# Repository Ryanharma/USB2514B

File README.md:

# USB2514B
USB Hub design project on Kicad => schematic + pcb layout (beginner)

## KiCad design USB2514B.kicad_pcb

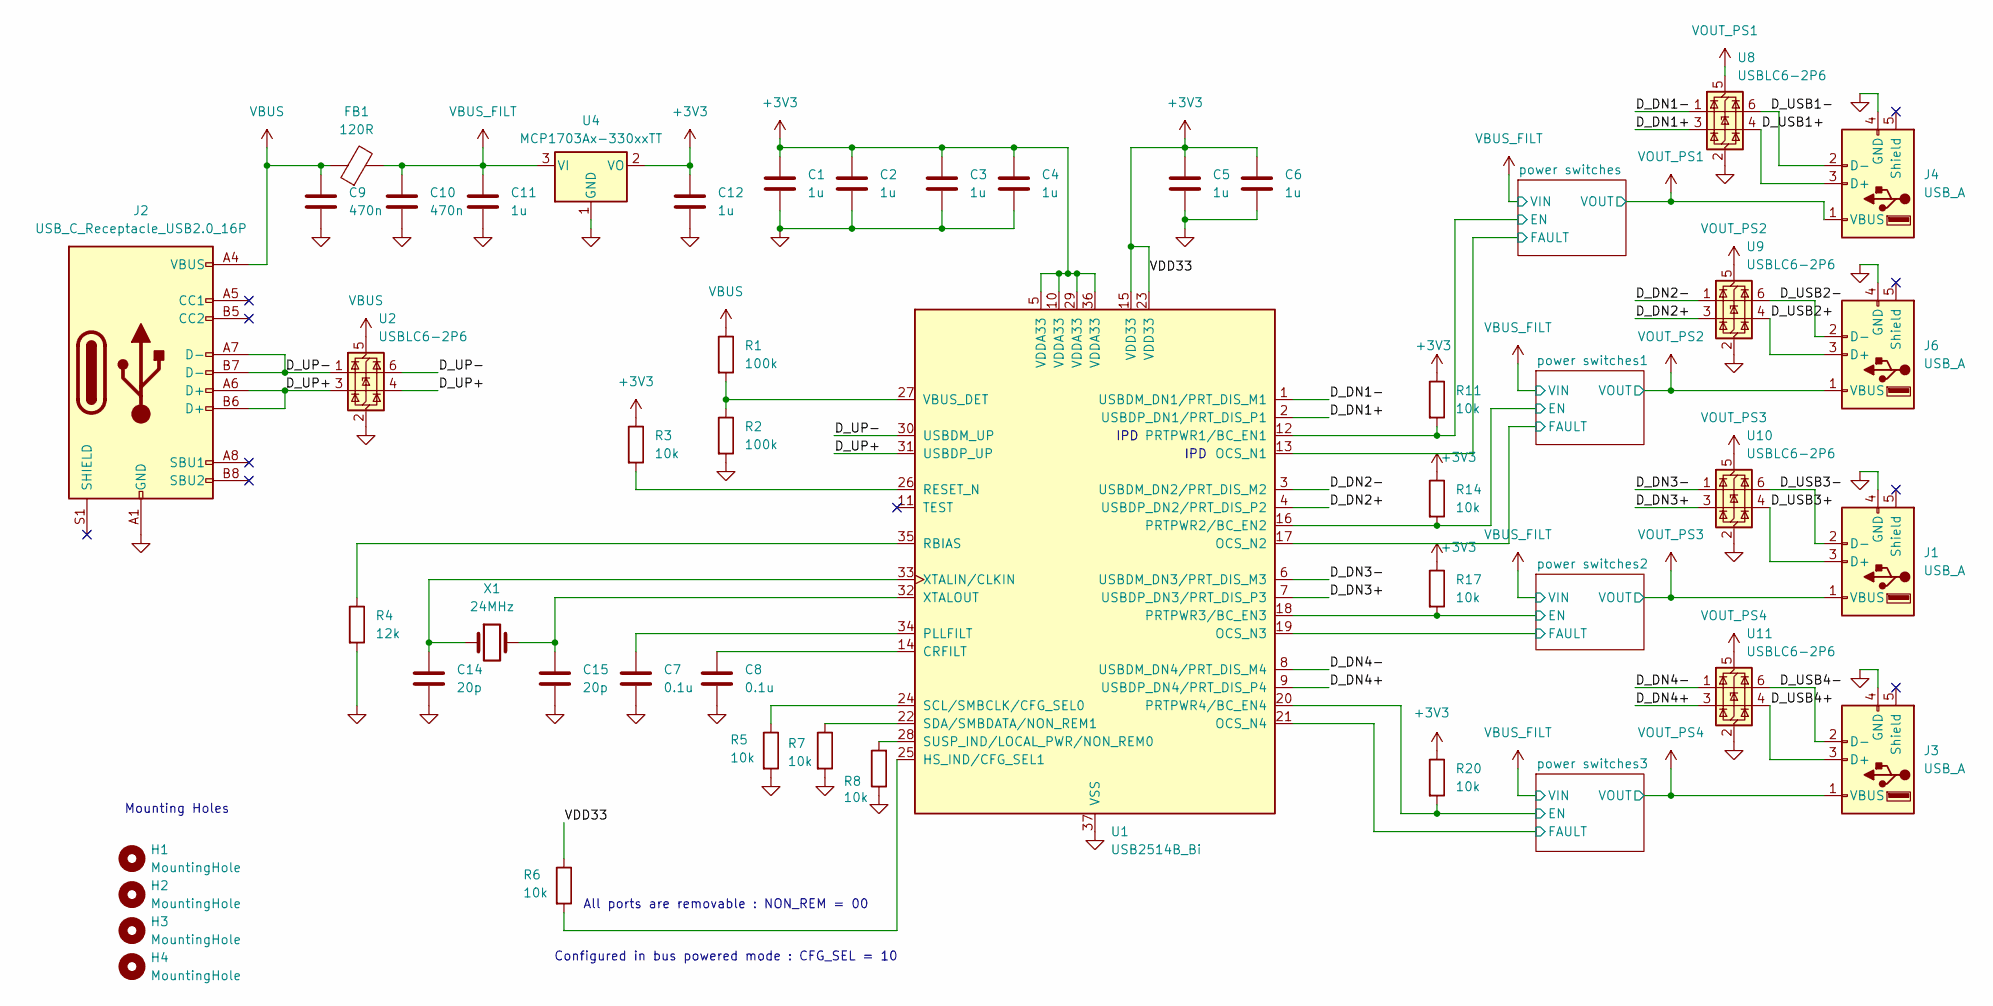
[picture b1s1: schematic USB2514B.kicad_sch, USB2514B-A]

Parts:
C1, C2, C3, C4, C5, C6, C11, C12: 1u; C_0402_1005Metric_Pad0.74x0.62mm_HandSolder; Manufacturer Part Number GXT155R61C105KE01D; LCSC Part # C363938
C7, C8: 0.1u; C_1206_3216Metric_Pad1.33x1.80mm_HandSolder; Manufacturer Part Number 12065C104J4Z2A; LCSC Part # C6648471
C9, C10: 470n; C_0402_1005Metric_Pad0.74x0.62mm_HandSolder; Manufacturer Part Number GXT155R61C474KE01D; LCSC Part # C126625
C14, C15: 20p; C_0402_1005Metric_Pad0.74x0.62mm_HandSolder; Manufacturer Part Number GCM1555C1H200FA16D; LCSC Part # C1554
FB1: 120R; C_0603_1608Metric_Pad1.08x0.95mm_HandSolder; Manufacturer Part Number BLM18PG121SN1D; LCSC Part # C14709
H1, H2, H3, H4: MountingHole; MountingHole_2.2mm_M2
J1, J3, J4, J6: USB_A; USB_A_Molex_67643_Horizontal; Manufacturer Part Number 10502029K901A; LCSC Part # C2345
J2: USB_C_Receptacle_USB2.0_16P; USB_C_Receptacle_GCT_USB4105-xx-A_16P_TopMnt_Horizontal; Manufacturer Part Number UJ20-C-H-C-4-SMT-TR; LCSC Part # C36601498
R1: 100k; R_0402_1005Metric_Pad0.72x0.64mm_HandSolder; Manufacturer Part Number ERJ-H2RF1003X; LCSC Part # C25741
R2: 100k; R_0402_1005Metric_Pad0.72x0.64mm_HandSolder; Manufacturer Part Number RT0402WRD0710KL; LCSC Part # C25741
R3, R5, R6, R7, R8, R11, R14, R17, R20: 10k; R_0402_1005Metric_Pad0.72x0.64mm_HandSolder; Manufacturer Part Number RT0402WRD0710KL; LCSC Part # C25531
R4: 12k; R_0402_1005Metric_Pad0.72x0.64mm_HandSolder; Manufacturer Part Number AR0402FR-0712KL; LCSC Part # C144798
U1: USB2514B_Bi; QFN-36-1EP_6x6mm_P0.5mm_EP3.7x3.7mm; Manufacturer Part Number USB2514BI-AEZG-TR; LCSC Part # C58940
U2, U8, U9, U10, U11: USBLC6-2P6; SOT-666; Manufacturer Part Number USBLC6-2P6; LCSC Part # C15999
U4: MCP1703Ax-330xxTT; SOT-23; Manufacturer Part Number MCP1703AT-3302E/CBVAO; LCSC Part # C5236965
X1: 24MHz; Crystal_SMD_7050-2Pin_7.0x5.0mm_HandSoldering; Manufacturer Part Number ABLS7M2-24.000MHZ-D-2Y-T; LCSC Part # C6487089

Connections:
+3V3: C1.1, C2.1, C3.1, C4.1, C5.1, C6.1, C12.1, R3.1, R6.1, R11.1, R14.1, R17.1, R20.1, U1.5 (VDDA33), U1.10 (VDDA33), U1.15 (VDD33), U1.23 (VDD33), U1.29 (VDDA33), U1.36 (VDDA33), U4.2 (VO)
/D_DN1+: U1.2 (USBDP_DN1/PRT_DIS_P1), U8.3 (I/O2)
/D_DN1-: U1.1 (USBDM_DN1/PRT_DIS_M1), U8.1 (I/O1)
/D_DN2+: U1.4 (USBDP_DN2/PRT_DIS_P2), U9.3 (I/O2)
/D_DN2-: U1.3 (USBDM_DN2/PRT_DIS_M2), U9.1 (I/O1)
/D_DN3+: U1.7 (USBDP_DN3/PRT_DIS_P3), U10.3 (I/O2)
/D_DN3-: U1.6 (USBDM_DN3/PRT_DIS_M3), U10.1 (I/O1)
/D_DN4+: U1.9 (USBDP_DN4/PRT_DIS_P4), U11.3 (I/O2)
/D_DN4-: U1.8 (USBDM_DN4/PRT_DIS_M4), U11.1 (I/O1)
/D_UP+: J2.A6 (D+), J2.B6 (D+), U1.31 (USBDP_UP), U2.3 (I/O2), U2.4 (I/O2)
/D_UP-: J2.A7 (D-), J2.B7 (D-), U1.30 (USBDM_UP), U2.1 (I/O1), U2.6 (I/O1)
/D_USB1+: J4.3 (D+), U8.4 (I/O2)
/D_USB1-: J4.2 (D-), U8.6 (I/O1)
/D_USB2+: J6.3 (D+), U9.4 (I/O2)
/D_USB2-: J6.2 (D-), U9.6 (I/O1)
/D_USB3+: J1.3 (D+), U10.4 (I/O2)
/D_USB3-: J1.2 (D-), U10.6 (I/O1)
/D_USB4+: J3.3 (D+), U11.4 (I/O2)
/D_USB4-: J3.2 (D-), U11.6 (I/O1)
/power switches1/EN: R14.2, U1.16 (PRTPWR2/BC_EN2); also elsewhere on the board
/power switches1/FAULT: U1.17 (OCS_N2); also elsewhere on the board
/power switches2/EN: R17.2, U1.18 (PRTPWR3/BC_EN3); also elsewhere on the board
/power switches2/FAULT: U1.19 (OCS_N3); also elsewhere on the board
/power switches3/EN: R20.2, U1.20 (PRTPWR4/BC_EN4); also elsewhere on the board
/power switches3/FAULT: U1.21 (OCS_N4); also elsewhere on the board
/power switches/EN: R11.2, U1.12 (PRTPWR1/BC_EN1); also elsewhere on the board
/power switches/FAULT: U1.13 (OCS_N1); also elsewhere on the board
GND: C1.2, C2.2, C3.2, C4.2, C5.2, C6.2, C7.2, C8.2, C9.2, C10.2, C11.2, C12.2, C14.2, C15.2, J1.4 (GND), J2.A1 (GND), J2.A12 (GND), J2.B1 (GND), J2.B12 (GND), J3.4 (GND), J4.4 (GND), J6.4 (GND), R2.2, R4.2, R5.2, R7.2, R8.1, U1.37 (VSS), U2.2 (GND), U4.1 (GND), U8.2 (GND), U9.2 (GND), U10.2 (GND), U11.2 (GND); also elsewhere on the board
unnamed: C8.1, U1.14 (CRFILT)
unnamed: R6.2, U1.25 (HS_IND/CFG_SEL1)
unnamed: C7.1, U1.34 (PLLFILT)
unnamed: R4.1, U1.35 (RBIAS)
unnamed: R3.2, U1.26 (RESET_N)
unnamed: R5.1, U1.24 (SCL/SMBCLK/CFG_SEL0)
unnamed: R7.1, U1.22 (SDA/SMBDATA/NON_REM1)
unnamed: R8.2, U1.28 (SUSP_IND/LOCAL_PWR/NON_REM0)
unnamed: R1.2, R2.1, U1.27 (VBUS_DET)
unnamed: C14.1, U1.33 (XTALIN/CLKIN), X1.1
unnamed: C15.1, U1.32 (XTALOUT), X1.2
VBUS: C9.1, FB1.1, J2.A4 (VBUS), J2.A9 (VBUS), J2.B4 (VBUS), J2.B9 (VBUS), R1.1, U2.5 (VBUS)
VBUS_FILT: C10.1, C11.1, FB1.2, U4.3 (VI); also elsewhere on the board
VOUT_PS1: J4.1 (VBUS), U8.5 (VBUS); also elsewhere on the board
VOUT_PS2: J6.1 (VBUS), U9.5 (VBUS); also elsewhere on the board
VOUT_PS3: J1.1 (VBUS), U10.5 (VBUS); also elsewhere on the board
VOUT_PS4: J3.1 (VBUS), U11.5 (VBUS); also elsewhere on the board

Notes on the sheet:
All ports are removable : NON_REM = 00
Mounting Holes
IPD
Configured in bus powered mode : CFG_SEL = 10

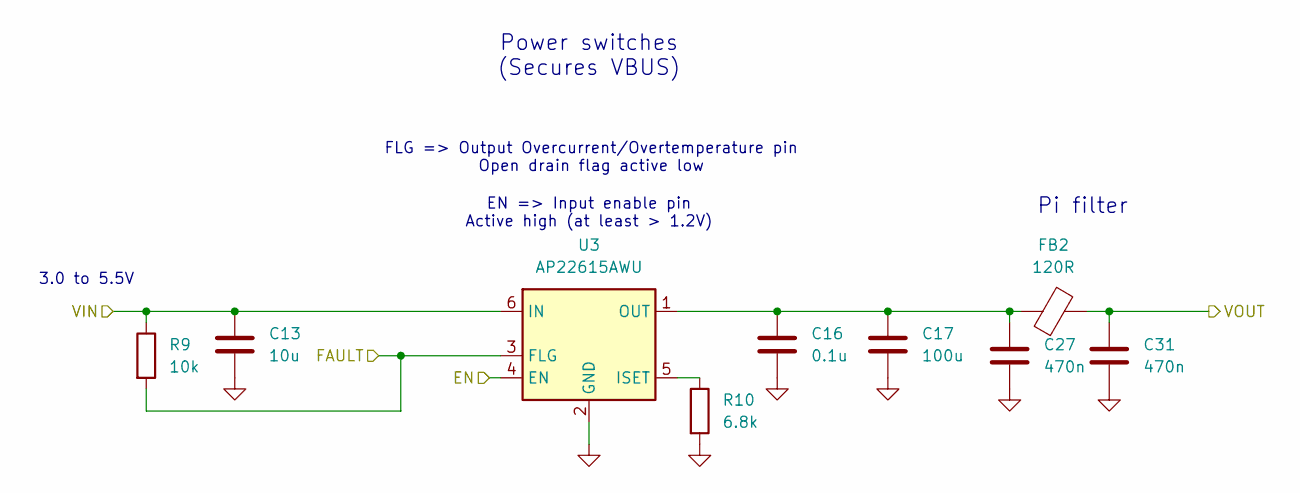
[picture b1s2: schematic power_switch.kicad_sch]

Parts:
C13: 10u; C_0603_1608Metric_Pad1.08x0.95mm_HandSolder; Manufacturer Part Number GXT188R61C106KE13D; LCSC Part # C711098
C16: 0.1u; C_0402_1005Metric_Pad0.74x0.62mm_HandSolder; Manufacturer Part Number GXT155R71E104KE01D; LCSC Part # C7200356
C17: 100u; C_1206_3216Metric_Pad1.33x1.80mm_HandSolder; Manufacturer Part Number GRM31CR61A107MEA8K; LCSC Part # C3841584
C27, C31: 470n; C_0402_1005Metric_Pad0.74x0.62mm_HandSolder; Manufacturer Part Number GXT155R61C474KE01D; LCSC Part # C126625
FB2: 120R; C_0603_1608Metric_Pad1.08x0.95mm_HandSolder; Manufacturer Part Number BLM18PG121SN1D; LCSC Part # C14709
R9: 10k; R_0402_1005Metric_Pad0.72x0.64mm_HandSolder; Manufacturer Part Number RT0402WRD0710KL; LCSC Part # C25531
R10: 6.8k; R_0402_1005Metric_Pad0.72x0.64mm_HandSolder; Manufacturer Part Number ERJ-H2RD6801X; LCSC Part # C5634705
U3: AP22615AWU; SOT-23-6; Manufacturer Part Number AP22615AWU-7; LCSC Part # C2680357

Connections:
/power switches/EN: U3.4 (EN); also elsewhere on the board
/power switches/FAULT: R9.2, U3.3 (FLG); also elsewhere on the board
GND: C13.2, C16.2, C17.2, C27.2, C31.2, R10.2, U3.2 (GND); also elsewhere on the board
unnamed: R10.1, U3.5 (ISET)
unnamed: C16.1, C17.1, C27.1, FB2.1, U3.1 (OUT)
VBUS_FILT: C13.1, R9.1, U3.6 (IN); also elsewhere on the board
VOUT_PS1: C31.1, FB2.2; also elsewhere on the board

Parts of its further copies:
C18, C21, C24: 10u; C_0603_1608Metric_Pad1.08x0.95mm_HandSolder; Manufacturer Part Number GXT188R61C106KE13D; LCSC Part # C711098
C19, C22, C25: 0.1u; C_0402_1005Metric_Pad0.74x0.62mm_HandSolder; Manufacturer Part Number GXT155R71E104KE01D; LCSC Part # C7200356
C20, C23, C26: 100u; C_1206_3216Metric_Pad1.33x1.80mm_HandSolder; Manufacturer Part Number GRM31CR61A107MEA8K; LCSC Part # C3841584
C28, C29, C30, C32, C33, C34: 470n; C_0402_1005Metric_Pad0.74x0.62mm_HandSolder; Manufacturer Part Number GXT155R61C474KE01D; LCSC Part # C126625
FB3, FB4, FB5: 120R; C_0603_1608Metric_Pad1.08x0.95mm_HandSolder; Manufacturer Part Number BLM18PG121SN1D; LCSC Part # C14709
R12, R15, R18: 10k; R_0402_1005Metric_Pad0.72x0.64mm_HandSolder; Manufacturer Part Number RT0402WRD0710KL; LCSC Part # C25531
R13, R16, R19: 6.8k; R_0402_1005Metric_Pad0.72x0.64mm_HandSolder; Manufacturer Part Number ERJ-H2RD6801X; LCSC Part # C5634705
U5, U6, U7: AP22615AWU; SOT-23-6; Manufacturer Part Number AP22615AWU-7; LCSC Part # C2680357

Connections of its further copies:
/power switches1/EN: U5.4 (EN); also elsewhere on the board
/power switches1/FAULT: R12.2, U5.3 (FLG); also elsewhere on the board
/power switches2/EN: U6.4 (EN); also elsewhere on the board
/power switches2/FAULT: R15.2, U6.3 (FLG); also elsewhere on the board
/power switches3/EN: U7.4 (EN); also elsewhere on the board
/power switches3/FAULT: R18.2, U7.3 (FLG); also elsewhere on the board
GND: C18.2, C19.2, C20.2, C21.2, C22.2, C23.2, C24.2, C25.2, C26.2, C28.2, C29.2, C30.2, C32.2, C33.2, C34.2, R13.2, R16.2, R19.2, U5.2 (GND), U6.2 (GND), U7.2 (GND); also elsewhere on the board
unnamed: R13.1, U5.5 (ISET)
unnamed: C19.1, C20.1, C28.1, FB3.1, U5.1 (OUT)
unnamed: R16.1, U6.5 (ISET)
unnamed: C22.1, C23.1, C29.1, FB4.1, U6.1 (OUT)
unnamed: R19.1, U7.5 (ISET)
unnamed: C25.1, C26.1, C30.1, FB5.1, U7.1 (OUT)
VBUS_FILT: C18.1, C21.1, C24.1, R12.1, R15.1, R18.1, U5.6 (IN), U6.6 (IN), U7.6 (IN); also elsewhere on the board
VOUT_PS2: C32.1, FB3.2; also elsewhere on the board
VOUT_PS3: C33.1, FB4.2; also elsewhere on the board
VOUT_PS4: C34.1, FB5.2; also elsewhere on the board

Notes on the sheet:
3.0 to 5.5V
Power switches (Secures VBUS)
FLG => Output Overcurrent/Overtemperature pin Open drain flag active low
EN => Input enable pin Active high (at least > 1.2V)
Pi filter

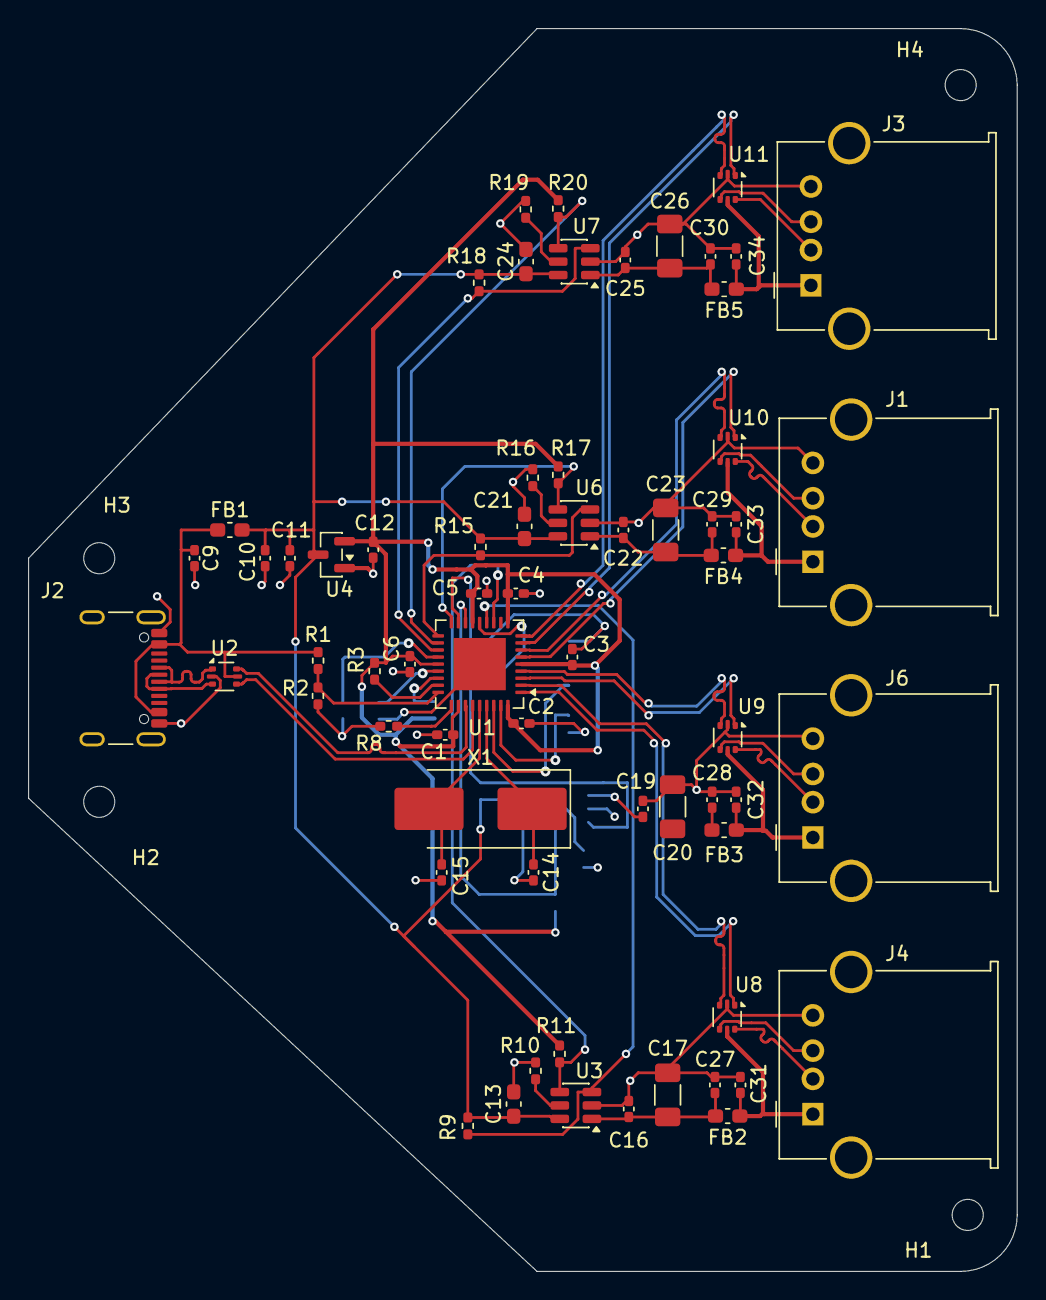
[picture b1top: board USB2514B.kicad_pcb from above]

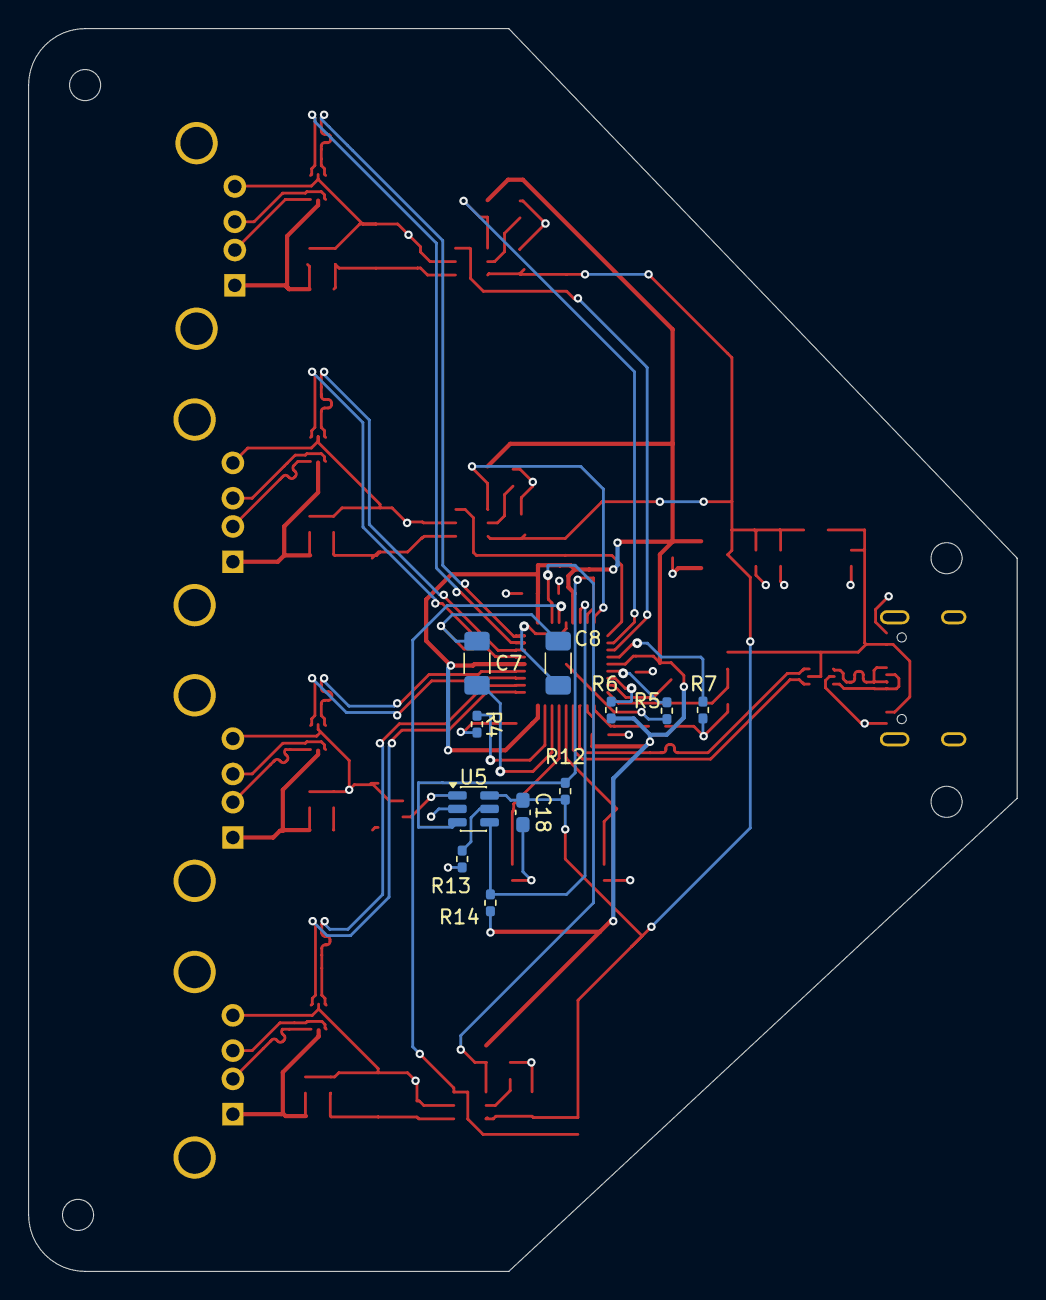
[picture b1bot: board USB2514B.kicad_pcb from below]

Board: 4 copper layers, 70.0 x 88.0 mm, 80 parts (11 on the bottom side), 53 nets.

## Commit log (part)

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2026-06-28 Initialize Git repo with completed schematic and layout set-up for routing
2026-06-30 Added board outline via Edge.Cuts traces
